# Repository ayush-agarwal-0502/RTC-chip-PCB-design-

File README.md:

# RTC-chip-PCB-design-

This repository contains my work on the PCB design of RTC (Real Time Clock ) Chip implemented on a PCB (Printed Circuit Board) . The PCB is designed using EagleCAD , a professional PCB design software . The RTC Circuit is implemented using 555 timer as astable multivibrator , along with flip flops used as frequency dividers for the generated clock signal . 

__Skills :__ PCB Designing , 555 timer , Circuit Simulation , Digital Electronics 

## Project Results :

The proteus simulation , schematic , board and gerber file have been uploaded to this repository . The images of the results are as follows : 

* Gerber File (Final PCB design layout) images :

* Board File images :

* Eagle Circuit Schematic :

* Proteus Circuit Simulation :

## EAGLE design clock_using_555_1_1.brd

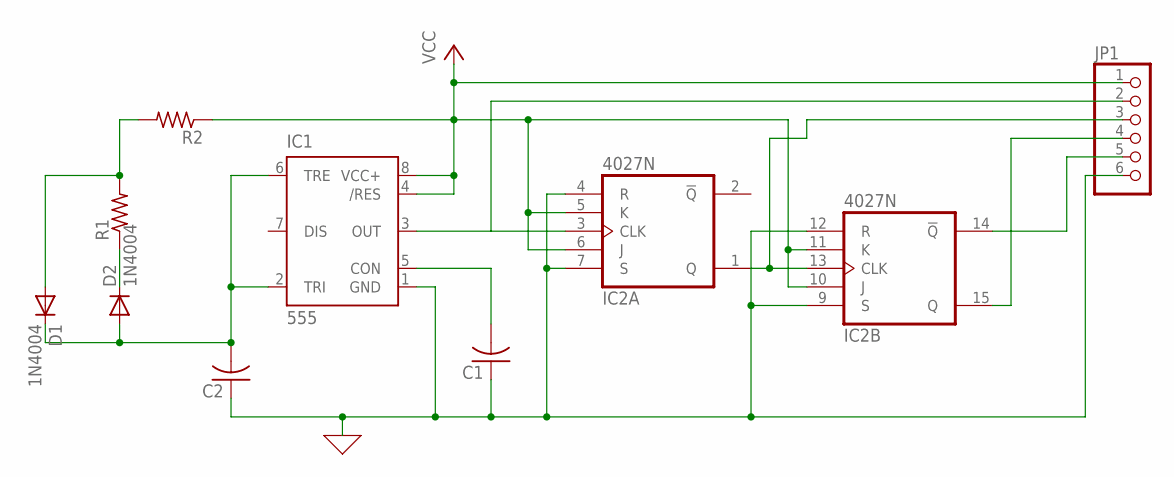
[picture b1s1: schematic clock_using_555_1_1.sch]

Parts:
C1, C2: C-US025-025X050; C025-025X050
D1, D2: 1N4004; DO41-10
IC1: 555; DIP08
IC2: 4027N; DIL16
JP1: PINHD-1X6CB; 1X06-CLEANBIG
R1, R2: R-US_0204/5; 0204/5

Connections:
0: C1.1, C2.1, IC1.1 (GND), IC2.4 (R), IC2.7 (S), IC2.9 (S), IC2.12 (R), JP1.6
unnamed: C2.2, D1.C, D2.A, IC1.2 (TRI), IC1.6 (TRE)
unnamed: C1.2, IC1.5 (CON)
unnamed: D2.C, R1.1
unnamed: D1.A, R1.2, R2.2
unnamed: IC1.3 (OUT), IC2.3 (CLK), JP1.2
unnamed: IC2.1 (Q), IC2.13 (CLK), JP1.3
unnamed: IC2.15 (Q), JP1.4
unnamed: IC2.14 (!Q), JP1.5
VCC: IC1.4 (/RES), IC1.8 (VCC+), IC2.5 (K), IC2.6 (J), IC2.10 (J), IC2.11 (K), JP1.1, R2.1
VDD: IC2.16 (VDD)
VSS: IC2.8 (VSS)

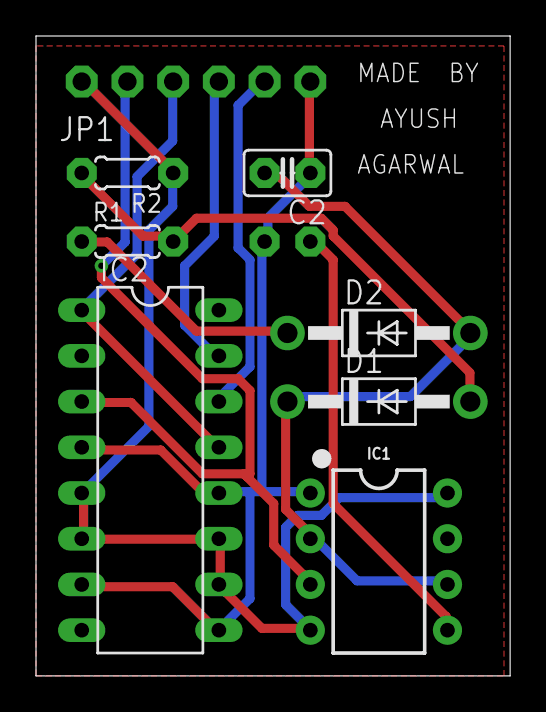
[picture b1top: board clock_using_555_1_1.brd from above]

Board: 2 copper layers, 26.3 x 35.5 mm, 9 parts (1 on the bottom side), 10 nets.

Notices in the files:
parts and their libraries:
SparkFun-IC-Special-Function: Licensing: Creative Commons ShareAlike 4.0 International - https://creativecommons.org/licenses/by-sa/4.0
